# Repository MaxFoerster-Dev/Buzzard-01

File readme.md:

# Buzzard-01

## The Rocket

### How I came up with the idea:

I watched a couple of [BPS.space](https://www.youtube.com/bpsspace) YouTube videos and thought _it's not gonna be that hard..._  
I remembered a c't magazine article about the program **[OpenRocket](#️-required-software--toolchain)** and I tried it. My final rocket was this:

### Why a Flight Computer?

Although it sounds like overkill, to put a flight computer on to the first ever build rocket, I did it.  
Since I was familiar with **[KiCad](#️-required-software--toolchain)** I choose to design the flight computer with KiCad.  
I came up with this design, featuring up to 3 sensors, a Raspberry Pi Pico and a place for the battery and an ON/OFF switch:

### Future Plans / Software

The next step is writing the flight software. I will probably use **[MicroPython](#️-required-software--toolchain)** to read the sensor data and control the rocket.

## Use of the Files

### .ork files (OpenRocket)

Open these files with **OpenRocket** to view or modify the rocket design and simulations.

- **How to open:** In OpenRocket, press `Ctrl+O` (or `Cmd+O` on Mac), navigate to the file, and open it.

### .kicad_pcb / .kicad_sch files (KiCad)

These files contain the schematics and PCB layout for the custom flight computer.

- **How to open:** Open **KiCad**, select `File` > `Open Project`, and select the project file in this directory.

### 3D Models (.obj / .stl)

These files contain the 3D-printable components of the rocket (like the nose cone or fins) and 3D renders of the electronics.

- **How to use:** Import the `.obj` files directly into your preferred 3D printing slicer (e.g., Cura, PrusaSlicer) or a CAD program (e.g., Blender, FreeCAD) for modifications.

### 🛠️ Required Software & Toolchain

To view, modify, or build this project, you will need the following software:

| Software | Purpose / Usage | Recommended Version |
| :--- | :--- | :--- |
| **[OpenRocket](https://openrocket.info)** | Rocket flight simulation and design (`.ork` files) | v23.09 or newer |
| **[KiCad](https://kicad.org)** | PCB Design & Schematics (`.kicad_*` files) | v8.x or newer |
| **[MicroPython](https://micropython.org)** | Flight controller firmware (Raspberry Pi Pico) | v1.22+ |
| **[Thonny](https://thonny.org)** or **[VS Code](https://code.visualstudio.com/download)** | Recommended IDE for flashing and writing MicroPython | Latest |
| **Any 3D Slicer** (e.g., [Cura](https://curaslicer.com/), [PrusaSlicer](https://www.prusa3d.com/p/prusaslicer/)) | Slicing `.stl`/`.obj` files for 3D printing | - |

## Security & Safety

Building and launching model rockets involves inherent physical and electrical risks. Please read the [Security Policy](https://github.com/MaxFoerster-Dev/Buzzard-01/security/policy) for important safety disclaimers, launch regulations, and instructions on how to report critical hardware or software flaws.

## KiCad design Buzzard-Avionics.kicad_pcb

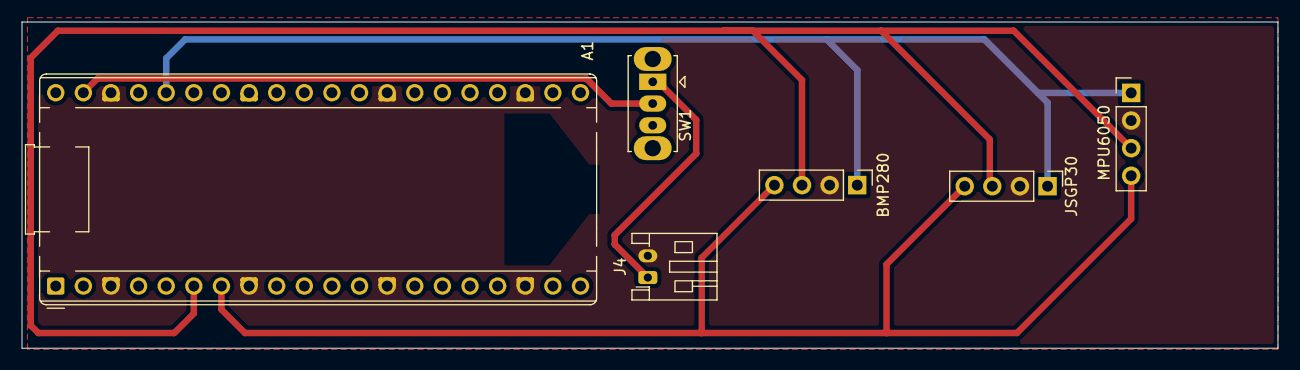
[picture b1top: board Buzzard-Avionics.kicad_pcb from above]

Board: 2 copper layers, 115.5 x 30.0 mm, 6 parts (0 on the bottom side), 6 nets.

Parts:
A1: RaspberryPi_Pico; RaspberryPi_Pico_Common_THT
BMP280: Conn_01x04_Pin; PinHeader_1x04_P2.54mm_Vertical
J4: Conn_01x02_Socket; JST_PH_S2B-PH-K_1x02_P2.00mm_Horizontal
JSGP30: Conn_01x04_Pin; PinHeader_1x04_P2.54mm_Vertical
MPU6050: Conn_01x04_Pin; PinHeader_1x04_P2.54mm_Vertical
SW1: SW_SPDT; SW_Slide_SPDT_Straight_CK_OS102011MS2Q

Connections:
/+3V3: A1.36 (3V3), BMP280.1, JSGP30.1, MPU6050.1
/GND: A1.3 (GND), A1.8 (GND), A1.13 (GND), A1.18 (GND), A1.23 (GND), A1.28 (GND), A1.38 (GND), BMP280.2, J4.2, JSGP30.2, MPU6050.2
/I2C_SCL: A1.6 (GPIO4), BMP280.3, JSGP30.3, MPU6050.3
/I2C_SDA: A1.7 (GPIO5), BMP280.4, JSGP30.4, MPU6050.4
/V_BATT: J4.1, SW1.1 (A)
unnamed: A1.39 (VSYS), SW1.2 (B)

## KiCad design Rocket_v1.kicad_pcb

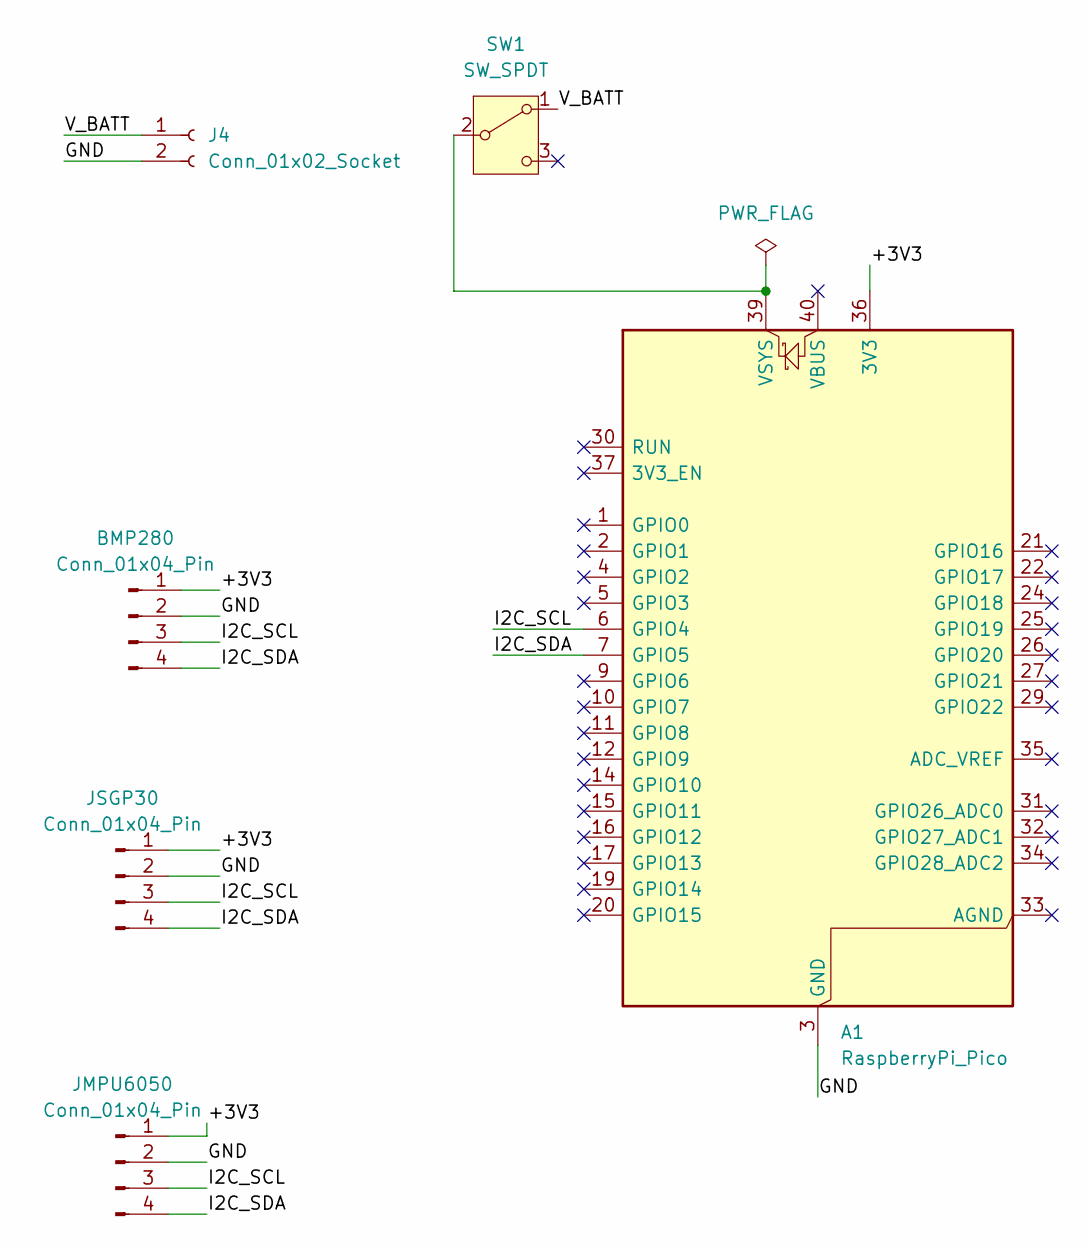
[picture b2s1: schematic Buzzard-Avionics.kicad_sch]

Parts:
A1: RaspberryPi_Pico; RaspberryPi_Pico_Common_THT
BMP280: Conn_01x04_Pin; PinHeader_1x04_P2.54mm_Vertical
J4: Conn_01x02_Socket; JST_PH_S2B-PH-K_1x02_P2.00mm_Horizontal
JMPU6050: Conn_01x04_Pin; PinHeader_1x04_P2.54mm_Vertical
JSGP30: Conn_01x04_Pin; PinHeader_1x04_P2.54mm_Vertical
SW1: SW_SPDT; SW_Slide_SPDT_Straight_CK_OS102011MS2Q

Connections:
/+3V3: A1.36 (3V3), BMP280.1, JMPU6050.1, JSGP30.1
/GND: A1.3 (GND), A1.8 (GND), A1.13 (GND), A1.18 (GND), A1.23 (GND), A1.28 (GND), A1.38 (GND), BMP280.2, J4.2, JMPU6050.2, JSGP30.2
/I2C_SCL: A1.6 (GPIO4), BMP280.3, JMPU6050.3, JSGP30.3
/I2C_SDA: A1.7 (GPIO5), BMP280.4, JMPU6050.4, JSGP30.4
/V_BATT: J4.1, SW1.1 (A)
unnamed: A1.39 (VSYS), SW1.2 (B)

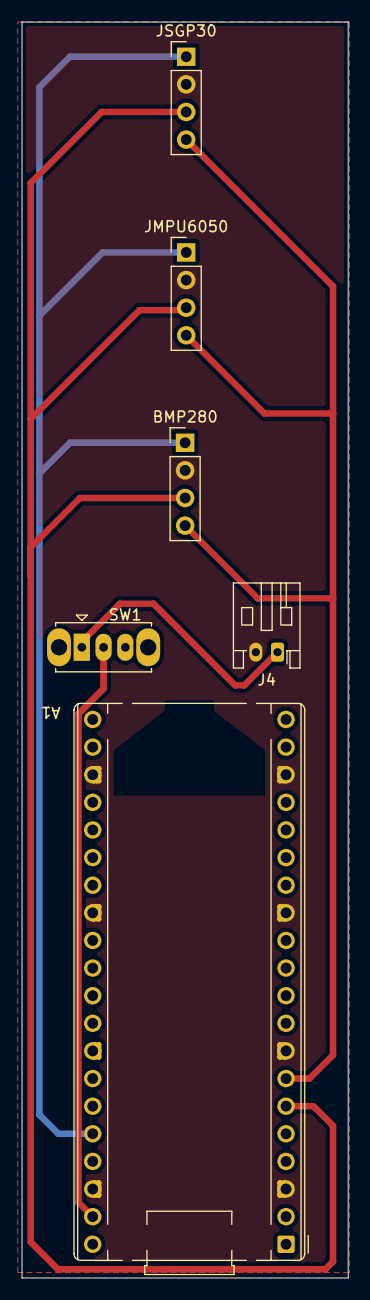
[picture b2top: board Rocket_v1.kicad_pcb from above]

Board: 2 copper layers, 30.0 x 115.5 mm, 6 parts (0 on the bottom side), 6 nets.

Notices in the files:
readme.md:
License: CC BY-NC-SA 4.0
